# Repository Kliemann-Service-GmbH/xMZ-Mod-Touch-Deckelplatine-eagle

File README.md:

# xMZ-Mod-Touch
## Eagle Dateien Bodenplatine

## Howto's
### Material Listen (BOM) erstellen

Die Material Listen werden aus den Eagle Zeichnungen gewonnen. Hierzu werden in
Eagle zunächst über den "design link" alle Bauteile in der Farnell Datenbank
gesucht. Anschließend wird diese Liste gespeicherti (Design Link Export).

* Dateiname: "Deckelplatine $VERSION-order.txt"

Danach wird das bom.ulp in Eagle ausgeführt. Folgende Einstellungen sind zu
wählen:

	Listen-Typ: Werte (Häckchen unter "Attribute auflisten" setzen)
	Ausgabeformat: CSV

Diese Datei wird ebenfalls gespeichert.

* Dateiname: "Deckelplatine $VERSION BOM.csv"

### Farnell BOM Import

Farnell bietet die Möglichkeit über eine Web GUI die BOM Daten in eine
Bestellung umzuwandeln.

Format der CSV Datei für den Import:
- 3 Spalten ("Anzahl;	Ordercode; Beschreibung")
- Dateiformat .xlsx oder .xls

#Produktionsdaten
## Dokumentation Boardlayout Dateien

Einige der wichtigsten Ebenen (Drill, Solder, Paste) wurden einzeln zusammen
mit der "Document" Ebene (Layer 48) als PDF gedruckt (Siehe Script generate_documentaiont.scr).
Dieses PDF kann mit dem Ghostscript tool `gs` in ein PDF gewandelt werden.

```
cd doc

gs -dBATCH -dNOPAUSE -q -sDEVICE=pdfwrite -sOutputFile=Deckelplatine-v1.0.0.pdf \
Deckelplatine-Placement_TOP.pdf \
Deckelplatine-TOP.pdf \
Deckelplatine-BOTTOM.pdf \
Deckelplatine-BOTTOM-Solder-Mask.pdf \
Deckelplatine-TOP-Paste-Mask.pdf \
Deckelplatine-Drill-Drawing.pdf \
```

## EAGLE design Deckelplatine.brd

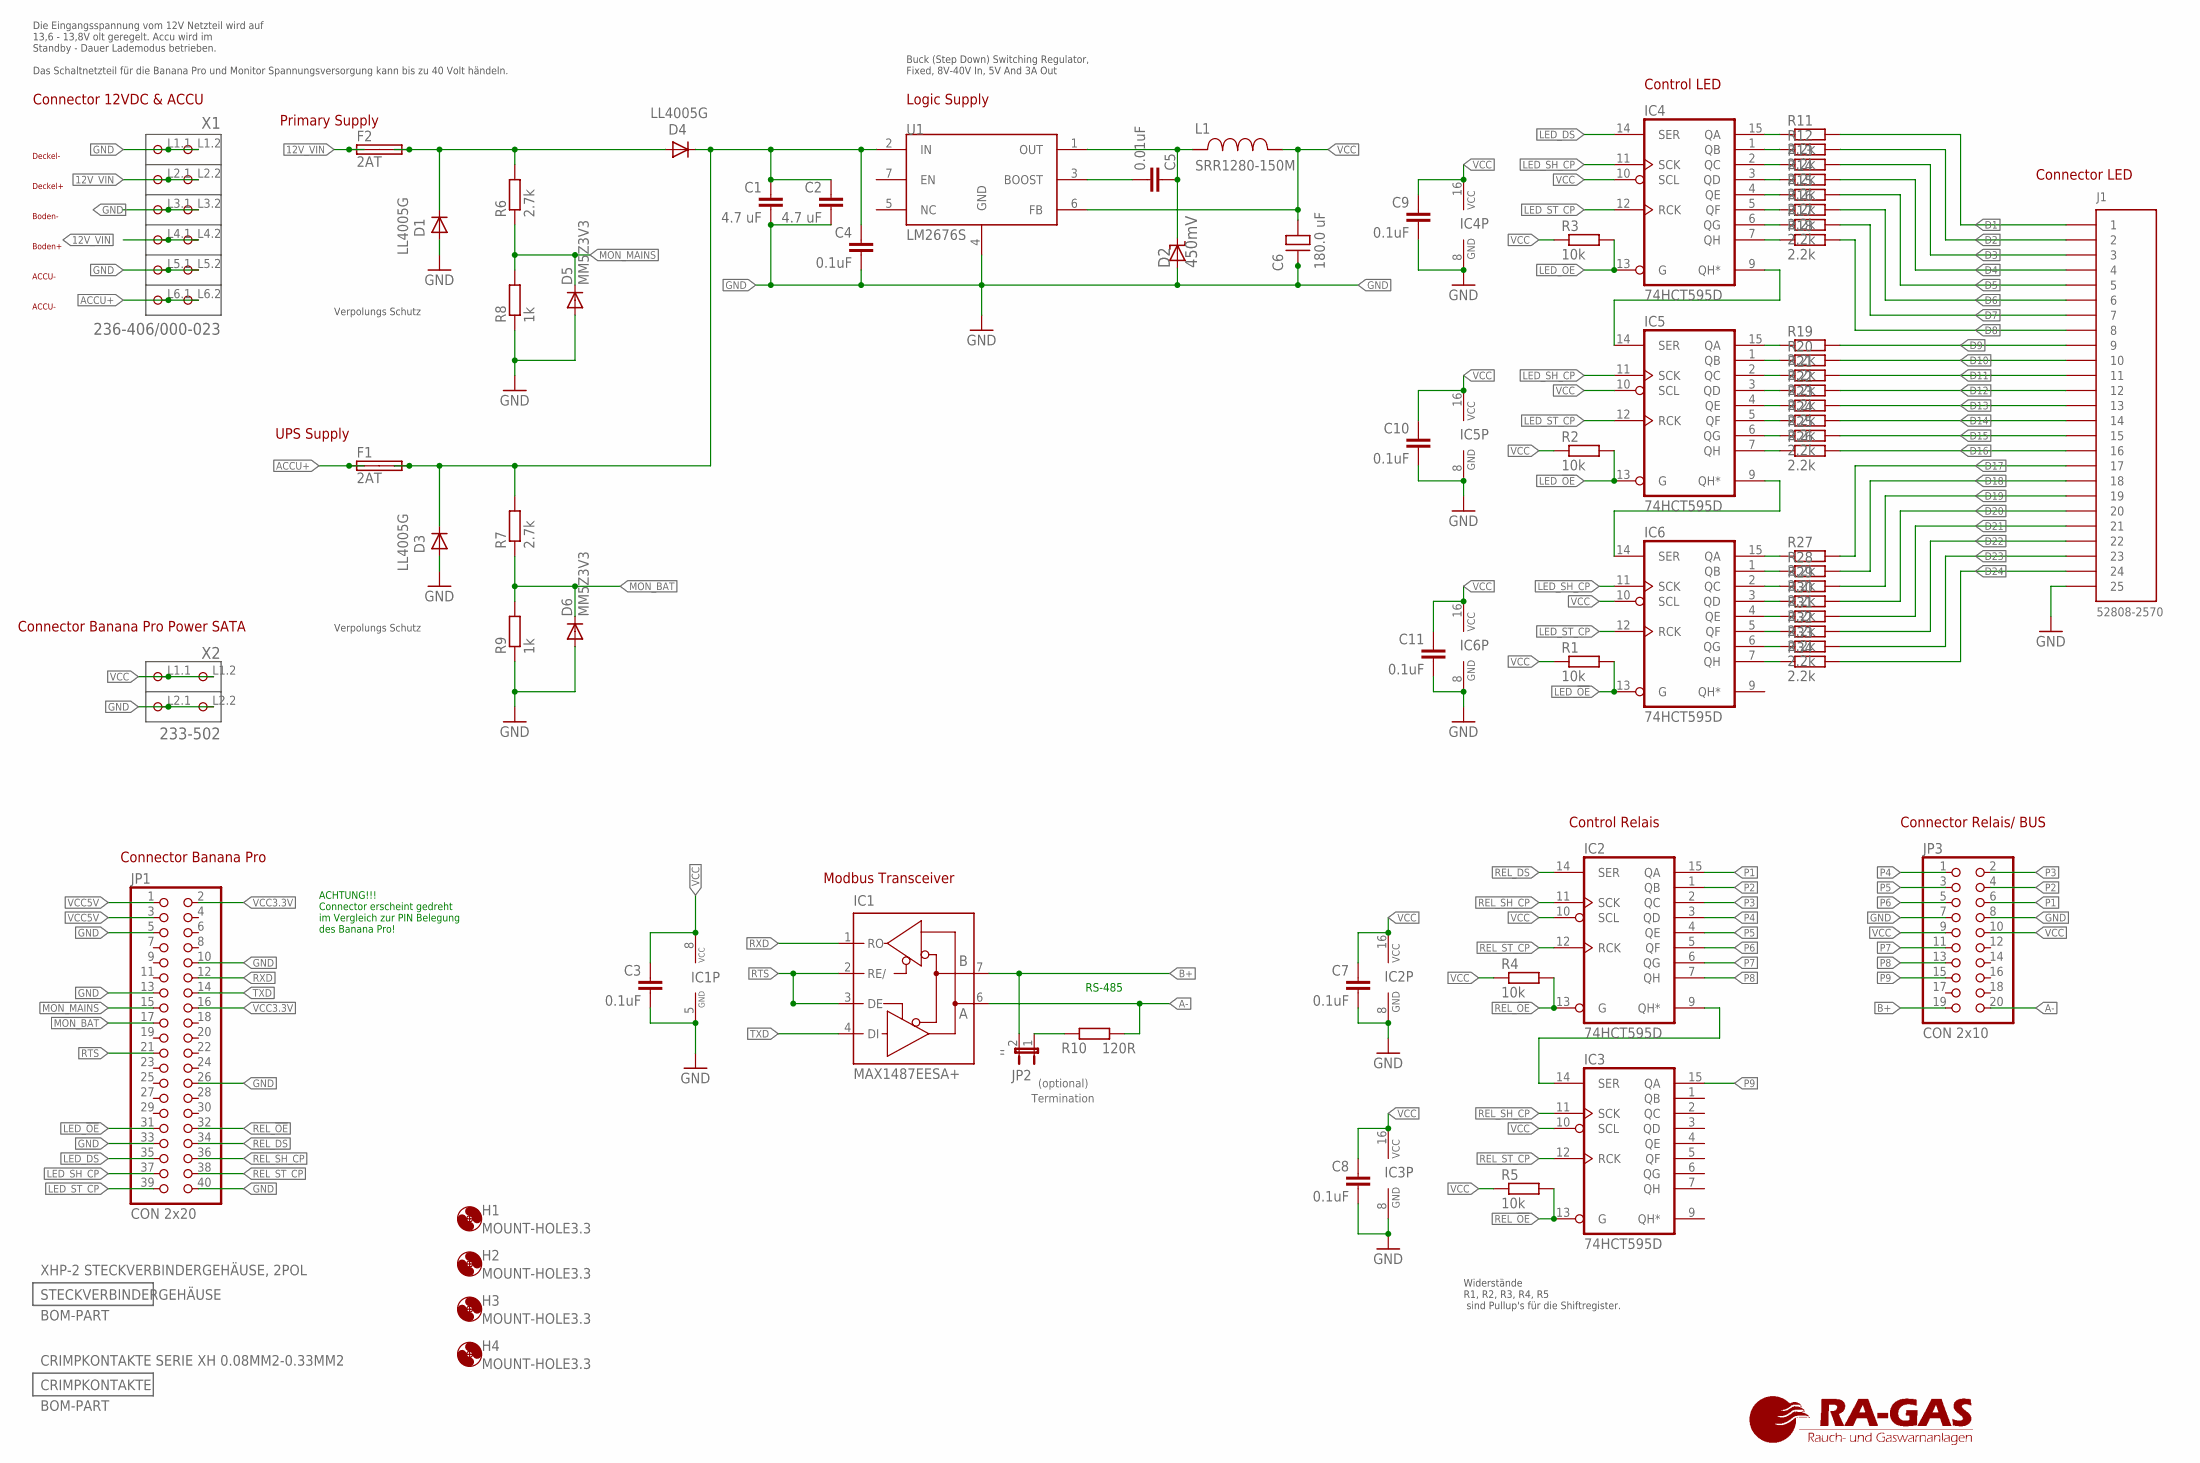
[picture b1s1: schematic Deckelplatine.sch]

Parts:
C1, C2: 4.7 uF; GRM21BR61E475MA12L; MPN GRM21BR61E475MA12L
C3, C7, C8, C9, C10, C11: 0.1uF; C0603; MPN C0603C104K8RACTU
C4: 0.1uF; 0805; MPN 08053C104KAT2A
C5: 0.01uF; GRM216R71H103KA01D; MPN GRM216R71H103KA01D
C6: 180.0 uF; SM_RADIAL_10MM; MPN 16SVP180MX
D1, D3, D4: LL4005G; MELF-MLL41; MPN LL4005G
D2: 450mV; SMB; MPN B340LB-13-F
D5, D6: MM5Z3V3; SOD523; MPN MM5Z3V3
F1, F2: 2AT; 01110005MR; MPN 01110005MR
H1, H2, H3, H4: MOUNT-HOLE3.3; 3,3
IC1: MAX1487EESA+; SO08; MPN MAX1487EESA+.
IC2, IC3, IC4, IC5, IC6: 74HCT595D; SO16; MPN 74HCT595D
J1: 52808-2570; MPN 52808-2570
JP1: CON 2x20; 2X20; MPN M20-6112045
JP2: ''; JP1; MPN 825433-2
JP3: CON 2x10; 2X10; MPN 5103308-5
L1: SRR1280-150M; SRR1280; MPN MSS1278-153MLD
R1, R2, R3, R4, R5: 10k; R0603; MPN CPF0603B10KE1
R6, R7: 2.7k; R0603; MPN CRCW08052K70FKEA
R8, R9: 1k; R0603; MPN RC0603FR-071KL.
R10: 120R; R1206; MPN CRGH1206F120R
R11, R12, R13, R14, R15, R16, R17, R18, R19, R20, R21, R22, R23, R24, R25, R26, R27, R28, R29, R30, R31, R32, R33, R34: 2.2k; R0603; MPN RC0603FR-072K2L.
U1: LM2676S; TO-263-7; MPN LM2676S-5.0/NOPB
X1: 236-406/000-023; P-236-406; MPN 236-406
X2: 233-502; P-233-502; MPN 233-502.

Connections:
12V_VIN: F2.1A, F2.1B, X1.L2.1 (P2.1), X1.L2.2 (P2.2), X1.L4.1 (P4.1), X1.L4.2 (P4.2)
A-: IC1.6 (A), JP3.20, R10.2
ACCU+: F1.1A, F1.1B, X1.L6.1 (P6.1), X1.L6.2 (P6.2)
B+: IC1.7 (B), JP2.2, JP3.19
D1: J1.1, R11.2
D2: J1.2, R12.2
D3: J1.3, R13.2
D4: J1.4, R14.2
D5: J1.5, R15.2
D6: J1.6, R16.2
D7: J1.7, R17.2
D8: J1.8, R18.2
D9: J1.9, R19.2
D10: J1.10, R20.2
D11: J1.11, R21.2
D12: J1.12, R22.2
D13: J1.13, R23.2
D14: J1.14, R24.2
D15: J1.15, R25.2
D16: J1.16, R26.2
D17: J1.17, R27.2
D18: J1.18, R28.2
D19: J1.19, R29.2
D20: J1.20, R30.2
D21: J1.21, R31.2
D22: J1.22, R32.2
D23: J1.23, R33.2
D24: J1.24, R34.2
GND: C1.2, C2.2, C3.2, C4.2, C6.2 (-), C7.2, C8.2, C9.2, C10.2, C11.2, D1.A, D2.A, D3.A, D5.A, D6.A, IC1.5 (GND), IC2.8 (GND), IC3.8 (GND), IC4.8 (GND), IC5.8 (GND), IC6.8 (GND), J1.25, JP1.5, JP1.10, JP1.13, JP1.26, JP1.33, JP1.40, JP3.7, JP3.8, R8.1, R9.1, U1.4 (GND), X1.L1.1 (P1.1), X1.L1.2 (P1.2), X1.L3.1 (P3.1), X1.L3.2 (P3.2), X1.L5.1 (P5.1), X1.L5.2 (P5.2), X2.L2.1 (P2.1), X2.L2.2 (P2.2)
LED_!OE: IC4.13 (G), IC5.13 (G), IC6.13 (G), JP1.31, R1.2, R2.2, R3.2
LED_DS: IC4.14 (SER), JP1.35
LED_SH_CP: IC4.11 (SCK), IC5.11 (SCK), IC6.11 (SCK), JP1.37
LED_ST_CP: IC4.12 (RCK), IC5.12 (RCK), IC6.12 (RCK), JP1.39
MON_BAT: D6.C, JP1.17, R7.1, R9.2
MON_MAINS: D5.C, JP1.15, R6.1, R8.2
unnamed: IC5.9 (QH*), IC6.14 (SER)
unnamed: IC2.9 (QH*), IC3.14 (SER)
unnamed: C1.1, C2.1, C4.1, D3.C, D4.C, F1.2A, F1.2B, R7.2, U1.2 (IN)
unnamed: IC4.9 (QH*), IC5.14 (SER)
unnamed: IC4.15 (QA), R11.1
unnamed: IC4.1 (QB), R12.1
unnamed: IC4.2 (QC), R13.1
unnamed: IC4.3 (QD), R14.1
unnamed: IC4.4 (QE), R15.1
unnamed: IC4.5 (QF), R16.1
unnamed: IC4.6 (QG), R17.1
unnamed: IC4.7 (QH), R18.1
unnamed: IC5.15 (QA), R19.1
unnamed: IC5.1 (QB), R20.1
unnamed: IC5.2 (QC), R21.1
unnamed: IC5.3 (QD), R22.1
unnamed: JP2.1, R10.1
unnamed: IC5.4 (QE), R23.1
unnamed: IC5.5 (QF), R24.1
unnamed: IC5.6 (QG), R25.1
unnamed: IC5.7 (QH), R26.1
unnamed: IC6.15 (QA), R27.1
unnamed: IC6.1 (QB), R28.1
unnamed: IC6.2 (QC), R29.1
unnamed: IC6.3 (QD), R30.1
unnamed: IC6.4 (QE), R31.1
unnamed: IC6.5 (QF), R32.1
unnamed: IC6.6 (QG), R33.1
unnamed: IC6.7 (QH), R34.1
unnamed: D1.C, D4.A, F2.2A, F2.2B, R6.2
unnamed: C5.2, U1.3 (BOOST)
unnamed: C5.1, D2.C, L1.1, U1.1 (OUT)
P1: IC2.15 (QA), JP3.6
P2: IC2.1 (QB), JP3.4
P3: IC2.2 (QC), JP3.2
P4: IC2.3 (QD), JP3.1
P5: IC2.4 (QE), JP3.3
P6: IC2.5 (QF), JP3.5
P7: IC2.6 (QG), JP3.11
P8: IC2.7 (QH), JP3.13
P9: IC3.15 (QA), JP3.15
REL_!OE: IC2.13 (G), IC3.13 (G), JP1.32, R4.2, R5.2
REL_DS: IC2.14 (SER), JP1.34
REL_SH_CP: IC2.11 (SCK), IC3.11 (SCK), JP1.36
REL_ST_CP: IC2.12 (RCK), IC3.12 (RCK), JP1.38
RTS: IC1.2 (RE/), IC1.3 (DE), JP1.21
RXD: IC1.1 (RO), JP1.12
TXD: IC1.4 (DI), JP1.14
VCC: C3.1, C6.1 (+), C7.1, C8.1, C9.1, C10.1, C11.1, IC1.8 (VCC), IC2.10 (SCL), IC2.16 (VCC), IC3.10 (SCL), IC3.16 (VCC), IC4.10 (SCL), IC4.16 (VCC), IC5.10 (SCL), IC5.16 (VCC), IC6.10 (SCL), IC6.16 (VCC), JP3.9, JP3.10, L1.2, R1.1, R2.1, R3.1, R4.1, R5.1, U1.6 (FB), X2.L1.1 (P1.1), X2.L1.2 (P1.2)
VCC3.3V: JP1.2, JP1.16
VCC5V: JP1.1, JP1.3

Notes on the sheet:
Connector Relais/ BUS
Connector Banana Pro
RS-485
Termination
(optional)
Modbus Transceiver
Connector LED
Control LED
Control Relais
Connector 12VDC & ACCU
UPS Supply
Primary Supply
Logic Supply
Connector Banana Pro Power SATA
ACCU-
ACHTUNG!!! Connector erscheint gedreht im Vergleich zur PIN Belegung des Banana Pro!
Boden-
Boden+
Deckel-
Deckel+
Widerstände R1, R2, R3, R4, R5 sind Pullup's für die Shiftregister.
Verpolungs Schutz
Buck (Step Down) Switching Regulator, Fixed, 8V-40V In, 5V And 3A Out
Die Eingangsspannung vom 12V Netzteil wird auf 13,6 - 13,8V olt geregelt. Accu wird im Standby - Dauer Lademodus betrieben. Das Schaltnetzteil für die Banana Pro und Monitor Spannungsversorgung kann bis zu 40 Volt händeln.

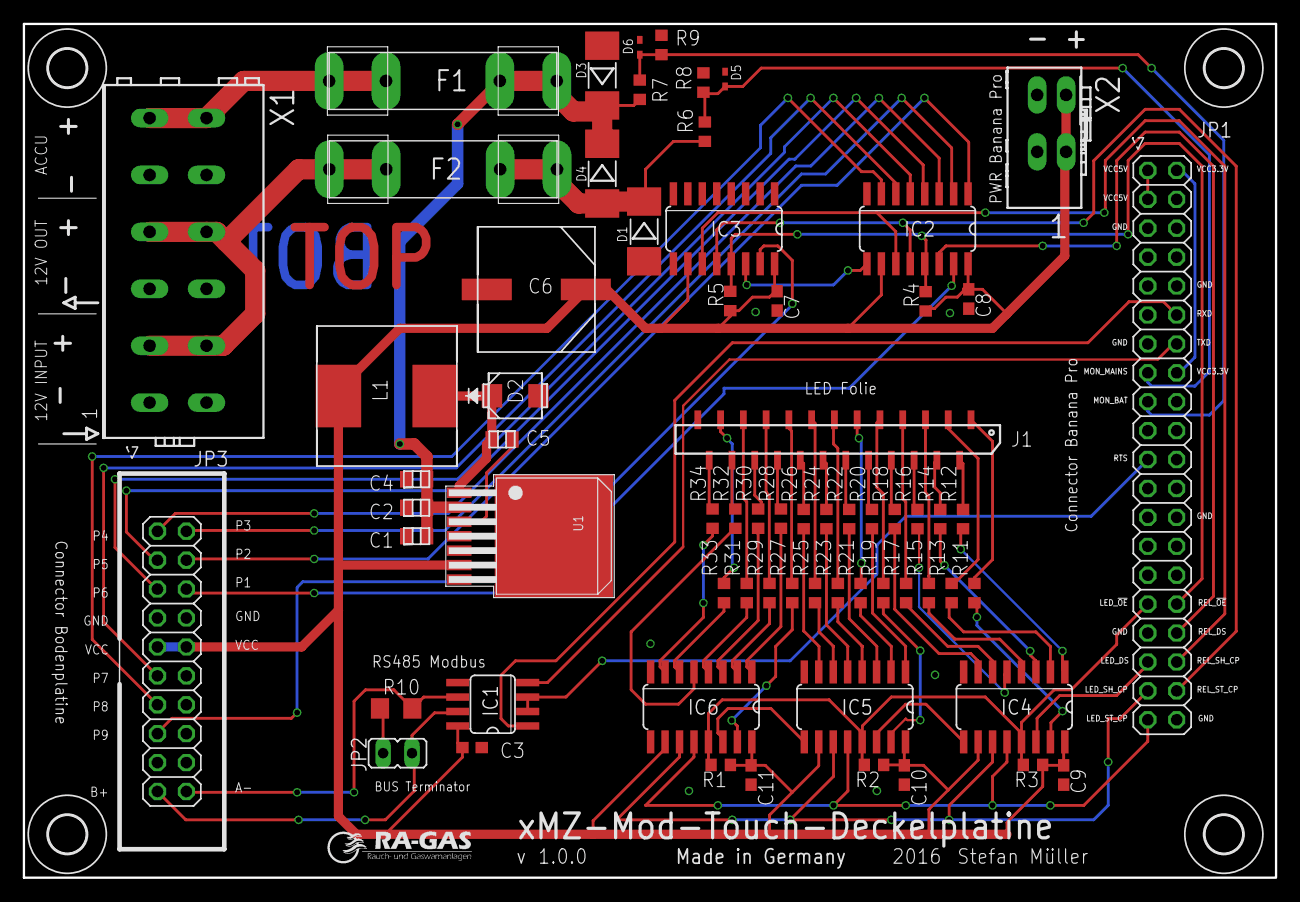
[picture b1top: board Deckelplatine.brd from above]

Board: 2 copper layers, 110.0 x 75.0 mm, 74 parts (0 on the bottom side), 86 nets.

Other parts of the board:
U$3: TEXT_NAME_VERSION_AUTHOR-SMALL
U$5: A3-LOC-RA-GAS
U$6: LOGO_RA-GAS-SMALL

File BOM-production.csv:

Qty,Value,Device,Package,Parts,Description,DATASHEETURL,DATASHEETURL_ALTERNATIVE,Datasheet,MF,MPN,OC_FARNELL,OC_FARNELL_ALTERNATIVE,OC_NEWARK,PARTNO
2,2AT,01110005MR,01110005MR,"F1, F2",Fuse Holder,http://www.farnell.com/datasheets/32844.pdf,,,LITTELFUSE,01110005MR,2413914,01110005MR,,
1,236-406/000-023,236-406/000-023,P-236-406,X1,Stand: 01.01.2014. D,http://www.farnell.com/datasheets/63479.pdf,,WAGO236_Connector Banana Pro Power SATA-WAGO236-402_WAGO236-403_WAGO236-404#WAG.pdf,WAGO,236-406,1283529,,,
2,2.7k,R-EU_R0603,R0603,"R6, R7","RESISTOR, European s",http://www.farnell.com/datasheets/1697337.pdf,,,VISHAY,CRCW08052K70FKEA,1469891,,,
1,LM2676S,LM2676S,TO-263-7,U1,LM2676,http://www.farnell.com/datasheets/1972849.pdf,,,TEXAS INSTRUMENTS,LM2676S-5.0/NOPB,1564684,,,
1,CON 2x20,PINHD-2X20,2X20,JP1,PIN HEADER,http://www.farnell.com/datasheets/34967.pdf,,,HARWIN,M20-6112045,1569232,1569230,,
1,MAX1487EESA+,MAX481CSA,SO08,IC1,RS485 TRANSEIVER,http://www.farnell.com/datasheets/3976.pdf,,,MAXIM INTEGRATED PRODUCTS,MAX1487EESA+.,1593310,8452210,,MAX481CSA
3,LL4005G,DIODE-MELF-MLL41,MELF-MLL41,"D1, D3, D4",DIODE,http://www.farnell.com/datasheets/54126.pdf,,,TAIWAN SEMICONDUCTOR,LL4005G,1625106,,,
5,10k,R-EU_R0603,R0603,"R1, R2, R3, R4, R5","RESISTOR, European s",http://www.farnell.com/datasheets/1786677.pdf,,,TE CONNECTIVITY / NEOHM,CPF0603B10KE1,1697388,,,
1,0.1uF,08053C104KAT2A,805,C4,,http://www.farnell.com/datasheets/1679506.pdf,,,AVX,08053C104KAT2A,1740665,,,
1,52808-2570,52808-2570,52808-2570,J1,Molex 25pin header,http://www.farnell.com/datasheets/1631601.pdf,,,MOLEX,52808-2570,1757123,,,
1,233-502,233-502,P-233-502,X2,"Serie 233,  Klemmenl",http://www.farnell.com/datasheets/1731610.pdf,,,WAGO,233-502.,1777096,,,
1,0.01uF,GRM216R71H103KA01D,GRM216R71H103KA01D,C5,,http://www.farnell.com/datasheets/608985.pdf,,,MURATA,GRM216R71H103KA01D,1828948,,,
1,450mV,B340LB-13-F,SMB,D2,,http://www.farnell.com/datasheets/639175.pdf,http://www.diodes.com/datasheets/ds30240.pdf,,DIODES INC.,B340LB-13-F,1843684,,,
5,74HCT595D,74HCT595D,SO16,"IC2, IC3, IC4, IC5, IC6",8-bit SHIFT REGISTER,http://www.farnell.com/datasheets/1886263.pdf,,,NXP,74HCT595D,2098004,,,SMD HC 595
6,0.1uF,C-EUC0603,C0603,"C3, C7, C8, C9, C10, C11","CAPACITOR, European ",http://www.farnell.com/datasheets/1851736.pdf,,,KEMET,C0603C104K8RACTU,2112833,,,"SMD TAN.0,1/35"
1,SRR1280-150M,SRR1280-150M,SRR1280,L1,,http://www.farnell.com/datasheets/1681956.pdf,,,COILCRAFT,MSS1278-153MLD,2288501,,,
1,120R,R-EU_R1206,R1206,R10,"RESISTOR, European s",http://www.farnell.com/datasheets/1755795.pdf,,,TE CONNECTIVITY,CRGH1206F120R,2332128,,,
1,180.0 uF,16SVP180MSM_RADIAL_10MM,SM_RADIAL_10MM,C6,,http://www.farnell.com/datasheets/1734357.pdf,,,PANASONIC ELECTRONIC COMPONENTS,16SVP180MX,2354685,,,RAD FC 560/35
2,4.7 uF,GRM21BR61E475MA12L,GRM21BR61E475MA12L,"C1, C2",,http://www.farnell.com/datasheets/1754705.pdf,http://www.murata.com/products/catalog/pdf/c02e.pdf,,MURATA,GRM21BR61E475MA12L,2362111,,,
1,CON 2x10,PINHD-2X10,2X10,JP3,PIN HEADER,http://www.farnell.com/datasheets/1498835.pdf,,,TE CONNECTIVITY / AMP,5103308-5,2452432,9689621,,
2, MM5Z3V3,DIODE-SOD523,SOD523,"D5, D6",DIODE,http://www.farnell.com/datasheets/1934593.pdf,,,FAIRCHILD SEMICONDUCTOR,MM5Z3V3,2454004,,,
1,'',JP1E,JP1,JP2,JUMPER,http://www.farnell.com/datasheets/27856.pdf,,,TE CONNECTIVITY / AMP,825433-2,3417645,,,
2,1k,R-EU_R0603,R0603,"R8, R9","RESISTOR, European s",http://www.farnell.com/datasheets/1868787.pdf,,,YAGEO (PHYCOMP),RC0603FR-071KL.,9238484,,,
24,2.2k,R-EU_R0603,R0603,"R11, R12, R13, R14, R15, R16, R17, R18, R19, R20, R21, R22, R23, R24, R25, R26, R27, R28, R29, R30, R31, R32, R33, R34","RESISTOR, European s",http://www.farnell.com/datasheets/1868787.pdf,,,YAGEO (PHYCOMP),RC0603FR-072K2L.,9238522,,,"SMD-0603 2,2K"
4,MOUNT-HOLE3.3,MOUNT-HOLE3.3,"3,3","H1, H2, H3, H4",MOUNTING HOLE with d,,,,,,unknown,,,

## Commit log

2016-02-25 Erste .gitignore Version
    Diese Version ignoriert die Eagle Sicherheitskopien.
2016-02-25 Import Deckelplatine Dateien aus dem master Branch
    Der Master Branch des alten Repos (Deckelplatine und Bodenplatine
    zusammen)
2016-02-25 Shift Register Pullup Widerstände eingefügt
2016-02-26 Realis Shift Register verschoben
    Die Schiebe Register für die Relais waren dem Stecker für die Verbindung zur Bodenplatine im Weg.
2016-03-08 BAT und MAINS Monitor
    Konnectoren in eigener Bibliothek 'Deckelplatine.lbr'
2016-03-08 Keine Airwire und DRC ist OK
    Sparkfun Design-Rule Check ist noch nicht erfüllt, hauptsächlich Winkel der Leiterbahnen und Abstände zu gering.
2016-03-08 PIN1 Nummern
    Kleiner gemacht und etwas verschoben so dass sie nicht mehr mit der Board Bezeichnung der Eingänge kollidieren.
2016-03-08 BOM und kontrolliert und eingfügt
2016-03-10 Bibliothek Export Script entfernt.
2016-03-10 Board auf Koordinaten 0x0 ausgerichtet
2016-03-10 Sichtbaren TOP und BOTTOM Layer eingefuegt
2016-03-10 Dokumentation eingefügt
2016-03-10 Fehler BOTTOM Layer Markierung gefixt
2016-08-15 Vergessener Commit zur Version 1.0.1

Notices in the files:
parts and their libraries:
bom: Copyright (C) 2010, Bob Starr
